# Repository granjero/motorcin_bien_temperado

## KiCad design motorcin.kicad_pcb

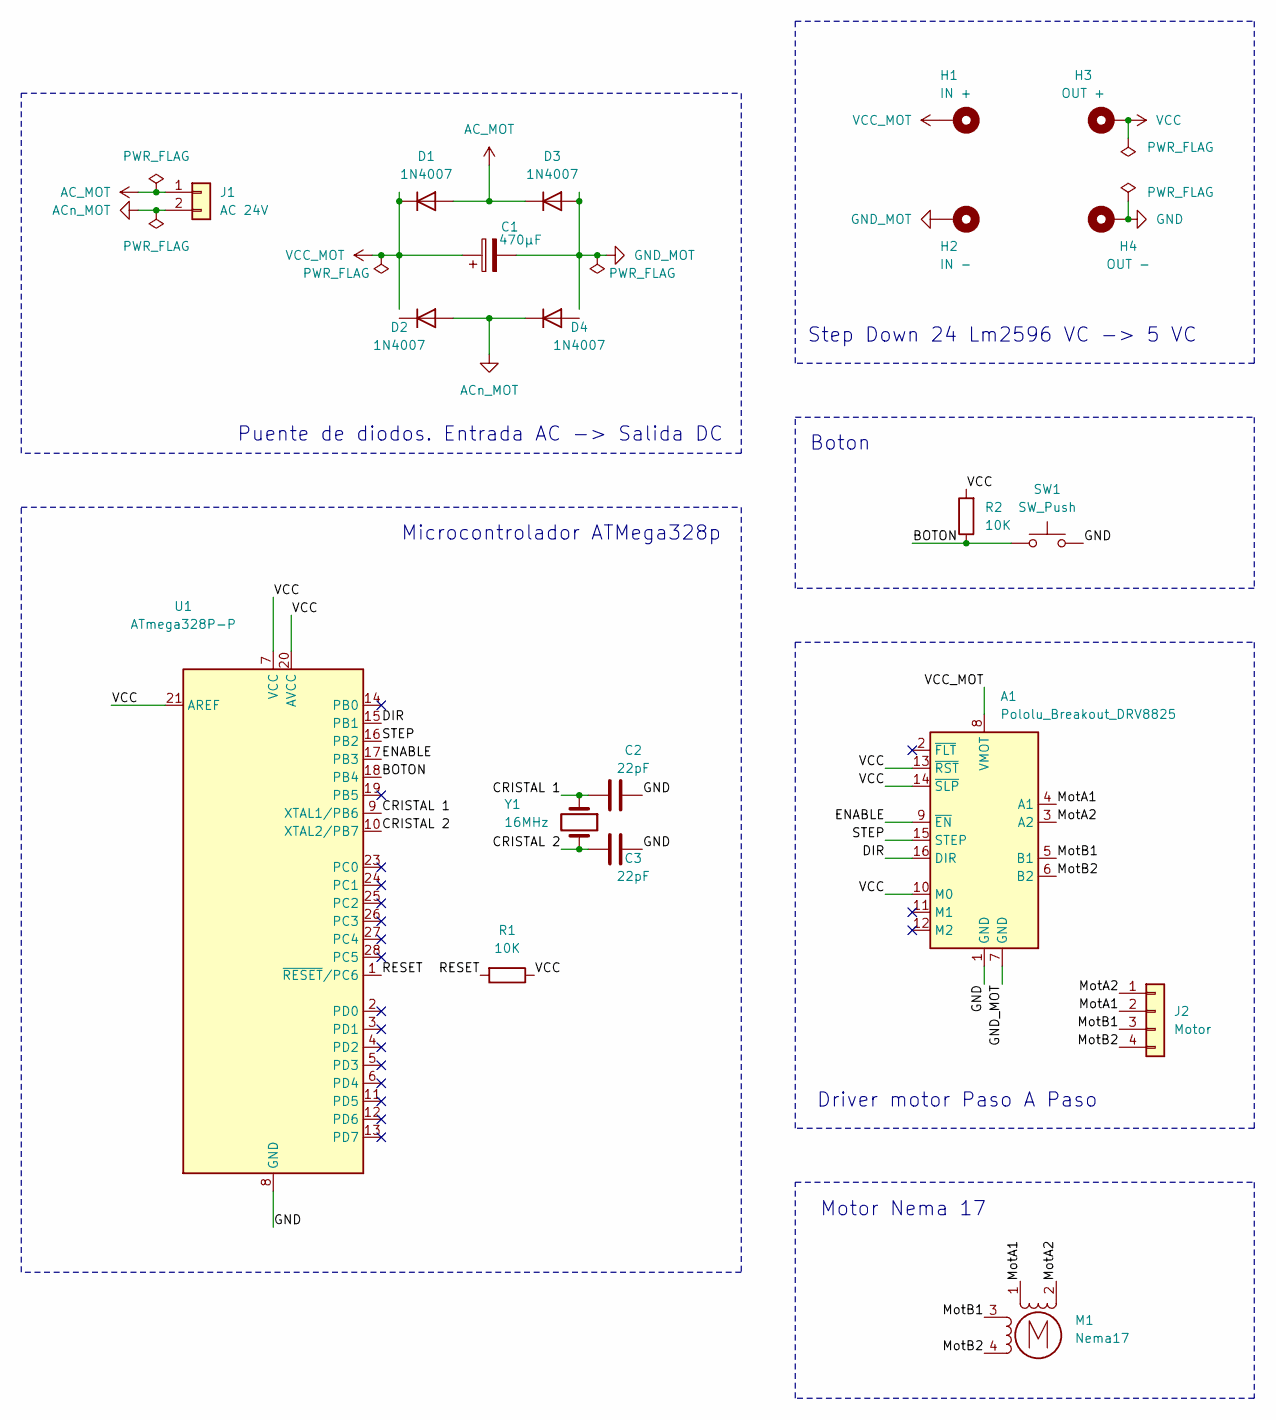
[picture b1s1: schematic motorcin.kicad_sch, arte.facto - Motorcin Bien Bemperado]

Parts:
A1: Pololu_Breakout_DRV8825; Pololu_Breakout-16_15.2x20.3mm
C1: 470μF; CP_Radial_D8.0mm_P2.50mm
C2, C3: 22pF; C_Disc_D5.0mm_W2.5mm_P5.00mm
D1, D2, D3, D4: 1N4007; D_DO-41_SOD81_P10.16mm_Horizontal
H1: IN +; MountingHole_2.2mm_M2_Pad
H2: IN -; MountingHole_2.2mm_M2_Pad
H3: OUT +; MountingHole_2.2mm_M2_Pad
H4: OUT -; MountingHole_2.2mm_M2_Pad
J1: AC 24V; PinHeader_1x02_P2.00mm_Horizontal
J2: Motor; PinSocket_1x04_P2.54mm_Vertical
M1: Nema17
R1, R2: 10K; R_Axial_DIN0204_L3.6mm_D1.6mm_P2.54mm_Vertical
SW1: SW_Push; SW_SPST_CK_RS282G05A3
U1: ATmega328P-P; DIP-28_W7.62mm
Y1: 16MHz; Crystal_HC49-4H_Vertical

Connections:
/BOTON: R2.1, SW1.1, U1.18 (PB4)
/CRISTAL 1: C2.1, U1.9 (XTAL1/PB6), Y1.1
/CRISTAL 2: C3.1, U1.10 (XTAL2/PB7), Y1.2
/DIR: A1.16 (DIR), U1.15 (PB1)
/ENABLE: A1.9 (~EN), U1.17 (PB3)
/MotA1: A1.4 (A1), J2.2, M1.1
/MotA2: A1.3 (A2), J2.1, M1.2 (-)
/MotB1: A1.5 (B1), J2.3, M1.3
/MotB2: A1.6 (B2), J2.4, M1.4
/RESET: R1.2, U1.1 (~RESET/PC6)
/STEP: A1.15 (STEP), U1.16 (PB2)
AC_MOT: D1.2 (A), D3.1 (K), J1.1
ACn_MOT: D2.2 (A), D4.1 (K), J1.2
GND: A1.1 (GND), C2.2, C3.2, H4.1, SW1.2, U1.8 (GND), U1.22 (GND)
GND_MOT: A1.7 (GND), C1.2, D3.2 (A), H2.1
VCC: A1.10 (M0), A1.13 (~RST), A1.14 (~SLP), H3.1, R1.1, R2.2, U1.7 (VCC), U1.20 (AVCC), U1.21 (AREF)
VCC_MOT: A1.8 (VMOT), C1.1, D1.1 (K), H1.1

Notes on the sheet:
Motor Nema 17
Step Down 24 Lm2596 VC -> 5 VC
Boton
Microcontrolador ATMega328p
Driver motor Paso A Paso
Puente de diodos. Entrada AC -> Salida DC

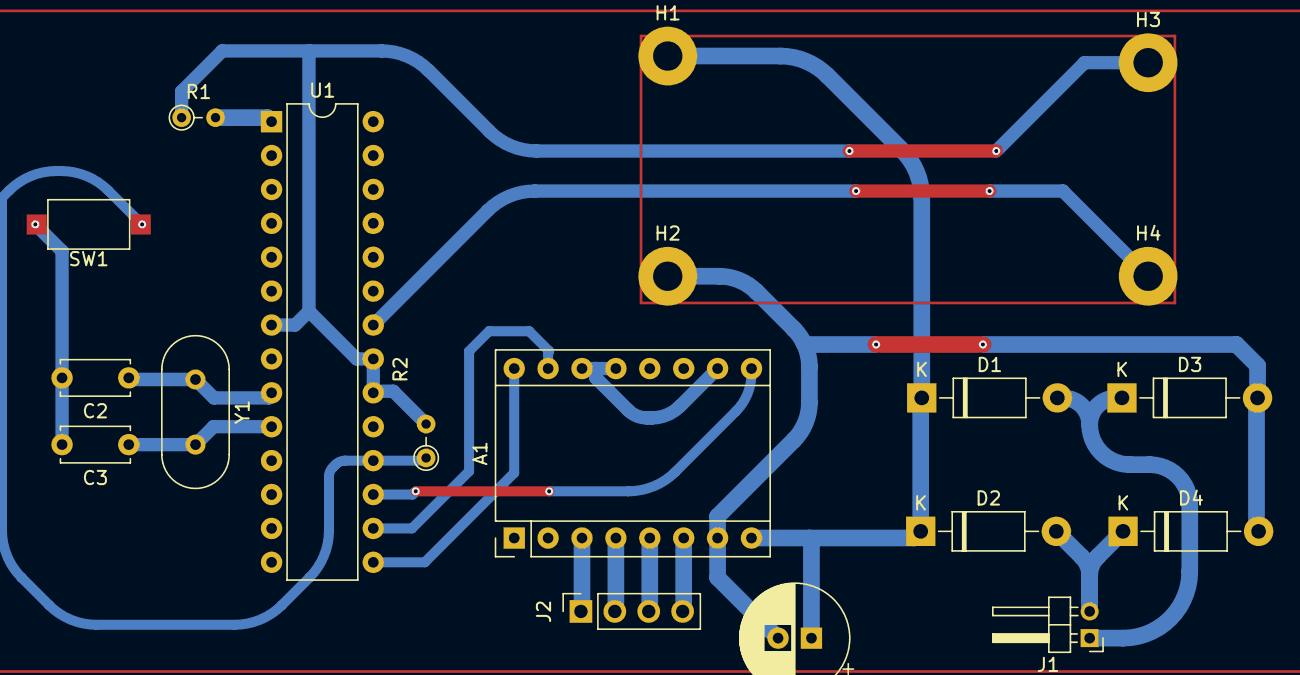
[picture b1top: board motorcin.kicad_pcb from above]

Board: 2 copper layers, 19 parts (0 on the bottom side), 17 nets.

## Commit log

2024-07-04 primer comit
2024-07-10 melodia completa, falta revisar y cambio de nombre al .ino
2024-07-10 andando melodia completa. revisarla.
2024-07-15 revision de la melodia
2024-08-04 version final?
2024-08-06 esquemáticos KiKad
2024-08-07 arreglos esteticos etc
